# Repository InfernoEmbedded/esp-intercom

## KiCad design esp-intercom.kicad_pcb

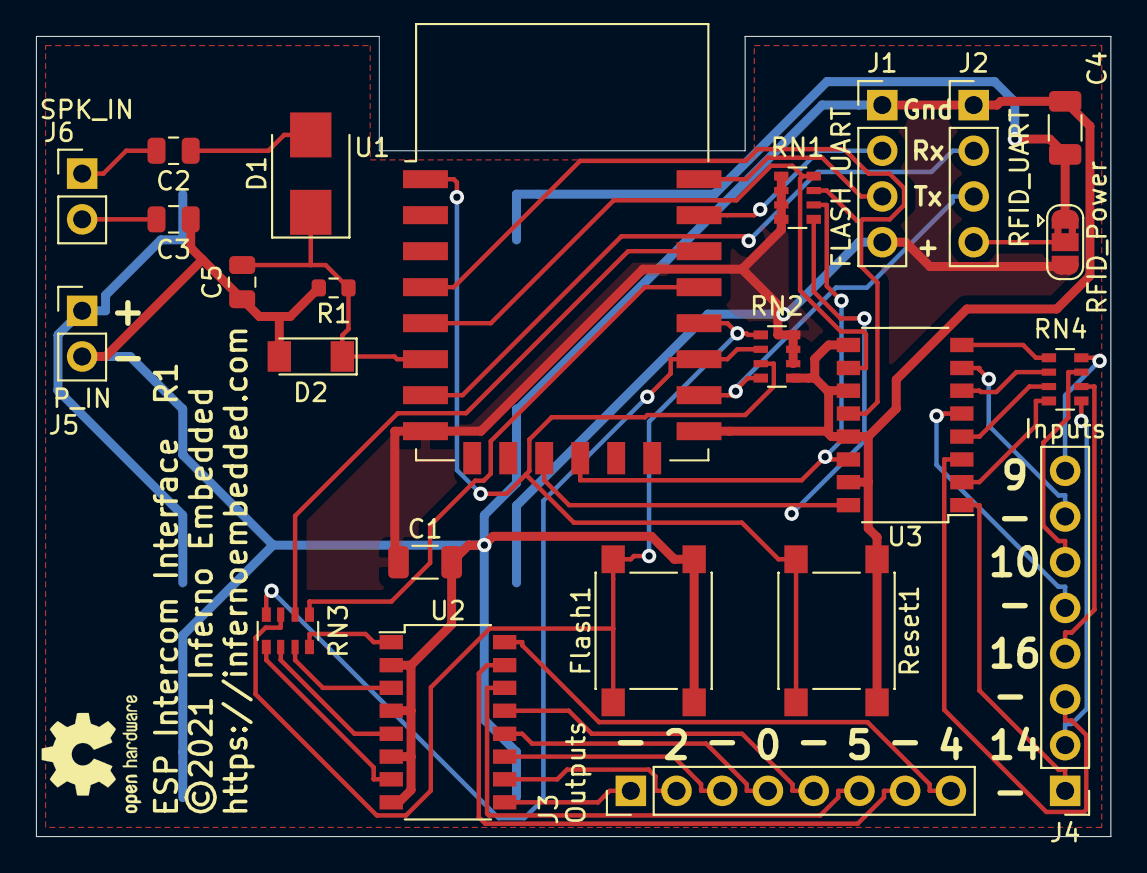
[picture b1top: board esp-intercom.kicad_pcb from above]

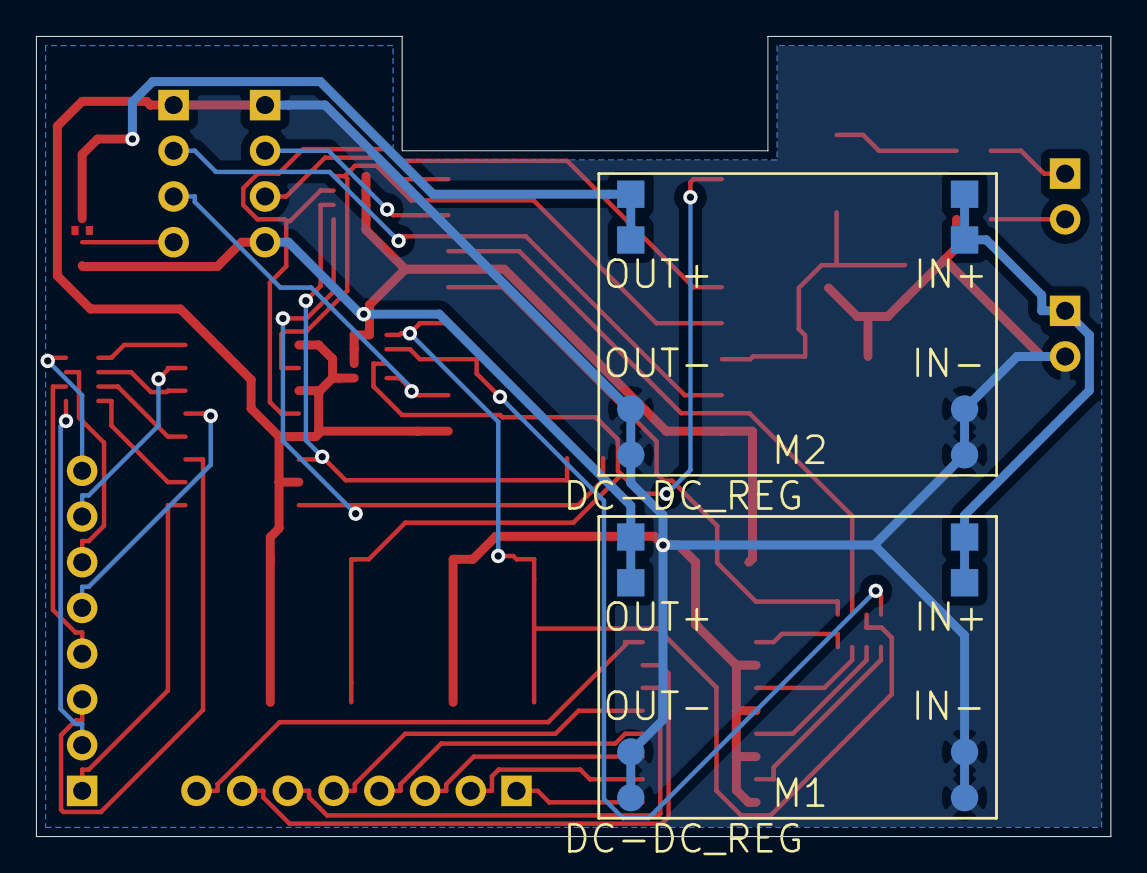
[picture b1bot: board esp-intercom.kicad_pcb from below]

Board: 2 copper layers, 59.7 x 44.5 mm, 26 parts (2 on the bottom side), 46 nets.

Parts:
C1, C4: 100uF; C_1206_3216Metric
C2, C3, C5: 47uF; C_0805_2012Metric
D1: D; D_SMB
D2: 3V; D_MiniMELF
Flash1: SW_Push; SW_Push_1P1T_NO_6x6mm_H9.5mm
J1: FLASH_UART; PinHeader_1x04_P2.54mm_Vertical
J2: RFID_UART; PinHeader_1x04_P2.54mm_Vertical
J3: Outputs; PinHeader_1x08_P2.54mm_Vertical
J4: Inputs; PinHeader_1x08_P2.54mm_Vertical
J5: P_IN; PinHeader_1x02_P2.54mm_Vertical
J6: SPK_IN; PinHeader_1x02_P2.54mm_Vertical
JP1: RFID_Power; SolderJumper-3_P1.3mm_Bridged2Bar12_RoundedPad1.0x1.5mm
M1, M2: DC-DC_REG; D-SUN_DC_DC_SMD
R1: 10k; R_0603_1608Metric
RN1, RN2: 10k; R_Array_Convex_4x0603
RN3, RN4: 100; R_Array_Convex_4x0603
Reset1: SW_Push; SW_Push_1P1T_NO_6x6mm_H9.5mm
U1: ESP-12F; ESP-12E
U2, U3: PC847; SOP-16_4.4x10.4mm_P1.27mm

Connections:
+3V3: C1.1, J1.4, JP1.3, M1.3, RN1.1, RN1.2, RN1.3, RN1.4, RN2.6, RN2.7, RN2.8, U1.8
+5V: C4.1, JP1.1, M2.3
+24V: J5.1, M1.1, M2.1
GND: C1.2, C3.1, C4.2, C5.1, D2.2, Flash1.2, J1.1, J2.1, J5.2, M1.2, M1.4, M2.2, M2.4, R1.2, RN2.5, Reset1.1, U1.15, U2.2, U2.4, U2.6, U2.8, U3.9, U3.11, U3.13, U3.15
unnamed: C2.1, D1.2
unnamed: C2.2, J6.1
unnamed: C3.2, J6.2
unnamed: C5.2, D1.1, D2.1, R1.1, U1.6
unnamed: Flash1.1, RN2.1, RN3.3, U1.18
unnamed: J1.2, U1.21
unnamed: J1.3, U1.22
unnamed: J2.2, U1.7
unnamed: J2.3, RN2.4, U1.16
unnamed: J2.4, JP1.2
unnamed: J3.1, U2.9
unnamed: J3.2, U2.10
unnamed: J3.3, U2.11
unnamed: J3.4, U2.12
unnamed: J3.5, U2.13
unnamed: J3.6, U2.14
unnamed: J3.7, U2.15
unnamed: J3.8, U2.16
unnamed: J4.1, U3.1
unnamed: J4.2, RN4.1
unnamed: J4.3, U3.3
unnamed: J4.4, RN4.2
unnamed: J4.5, U3.5
unnamed: J4.6, RN4.3
unnamed: J4.7, U3.7
unnamed: J4.8, RN4.4
unnamed: RN1.5, U1.11, U3.16
unnamed: RN1.6, U1.12, U3.14
unnamed: RN1.7, U1.4, U3.12
unnamed: RN1.8, U1.5, U3.10
unnamed: RN2.2, RN3.4, U1.17
unnamed: RN2.3, Reset1.2, U1.1
unnamed: RN3.1, U1.19
unnamed: RN3.2, U1.20
unnamed: RN3.5, U2.7
unnamed: RN3.6, U2.5
unnamed: RN3.7, U2.3
unnamed: RN3.8, U2.1
unnamed: RN4.5, U3.8
unnamed: RN4.6, U3.6
unnamed: RN4.7, U3.4
unnamed: RN4.8, U3.2

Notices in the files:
esp-intercom.kicad_pcb:
©2021 Inferno Embedded
